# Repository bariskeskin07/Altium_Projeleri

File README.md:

# Altium_Projeleri
Olusturdugum altium projeleri

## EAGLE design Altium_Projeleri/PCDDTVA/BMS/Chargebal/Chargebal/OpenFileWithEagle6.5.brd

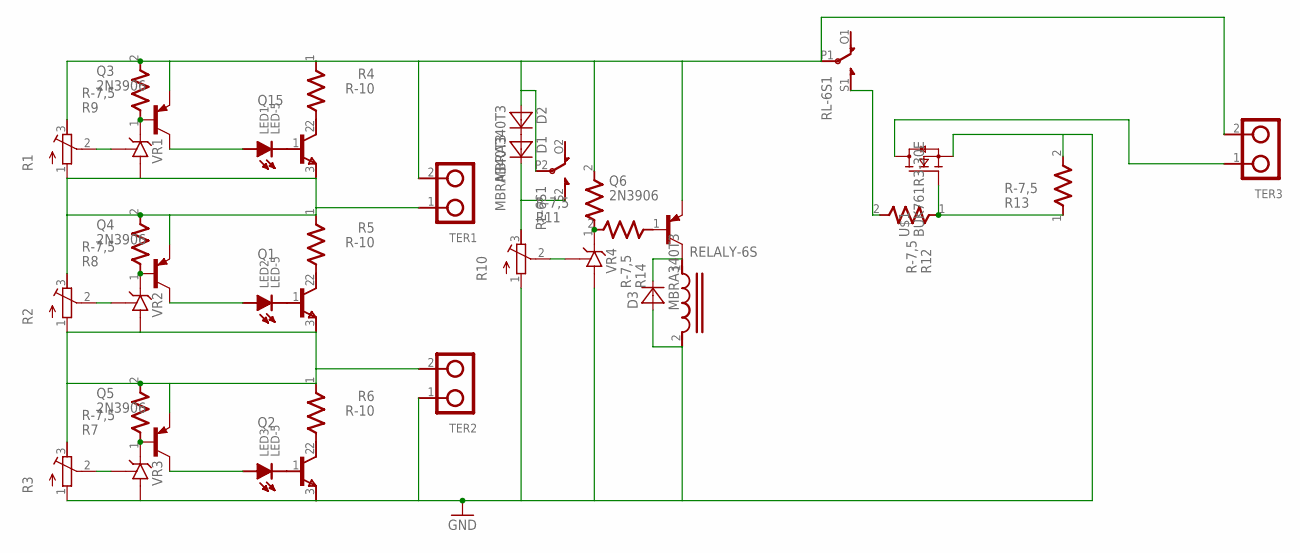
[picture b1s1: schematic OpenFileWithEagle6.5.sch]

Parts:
D1, D2, D3: MBRA340T3; SMA
LED1, LED2, LED3: LED-5; LED5
Q1, Q2, Q15: C1815; TO92L
Q3, Q4, Q5, Q6: 2N3906; TO92
R1, R2, R3, R10: R-TRIMM64W; RTRIM64W
R4, R5, R6: R-10
R7, R8, R9, R11, R12, R13, R14: R-7,5
RL-6S1: RELALY-6S; RELAY-6S
TER1, TER2, TER3: DOMINO-2; DOMI-2
U$1: BUK761R3-30E; SOT404
VR1, VR2, VR3, VR4: TL431CLP; TO92-CLP

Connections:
GND: D3.A, Q2.3 (E), R3.1 (A), R10.1 (A), R13.2, RL-6S1.2, TER2.1, U$1.3 (S), VR3.A, VR4.A
unnamed: LED1.K, Q15.1 (B)
unnamed: LED2.K, Q1.1 (B)
unnamed: LED3.K, Q2.1 (B)
unnamed: R10.2 (S), VR4.R
unnamed: R11.1, R14.2, VR4.C
unnamed: Q6.2 (B), R14.1
unnamed: R2.2 (S), VR2.R
unnamed: R3.2 (S), VR3.R
unnamed: Q3.2 (B), R9.1, VR1.C
unnamed: Q4.2 (B), R8.1, VR2.C
unnamed: Q5.2 (B), R7.1, VR3.C
unnamed: LED2.A, Q4.1 (C)
unnamed: LED3.A, Q5.1 (C)
unnamed: LED1.A, Q3.1 (C)
unnamed: Q15.2 (C), R4.2 (3)
unnamed: Q1.2 (C), R5.2 (3)
unnamed: Q2.2 (C), R6.2 (3)
unnamed: Q1.3 (E), Q5.3 (E), R2.1 (A), R3.3 (E), R6.1, R7.2, TER2.2, VR2.A
unnamed: Q4.3 (E), Q15.3 (E), R1.1 (A), R2.3 (E), R5.1, R8.2, TER1.1, VR1.A
unnamed: D2.A, Q3.3 (E), Q6.3 (E), R1.3 (E), R4.1, R9.2, R11.2, RL-6S1.P1, RL-6S1.P2, TER1.2, TER3.2
unnamed: R1.2 (S), VR1.R
unnamed: D3.C, Q6.1 (C), RL-6S1.1
unnamed: TER3.1, U$1.MB (D)
unnamed: D1.C, R10.3 (E), RL-6S1.S2 (S)
unnamed: R12.1, R13.1, U$1.1 (G)
unnamed: D1.A, D2.C
unnamed: R12.2, RL-6S1.S1 (S)

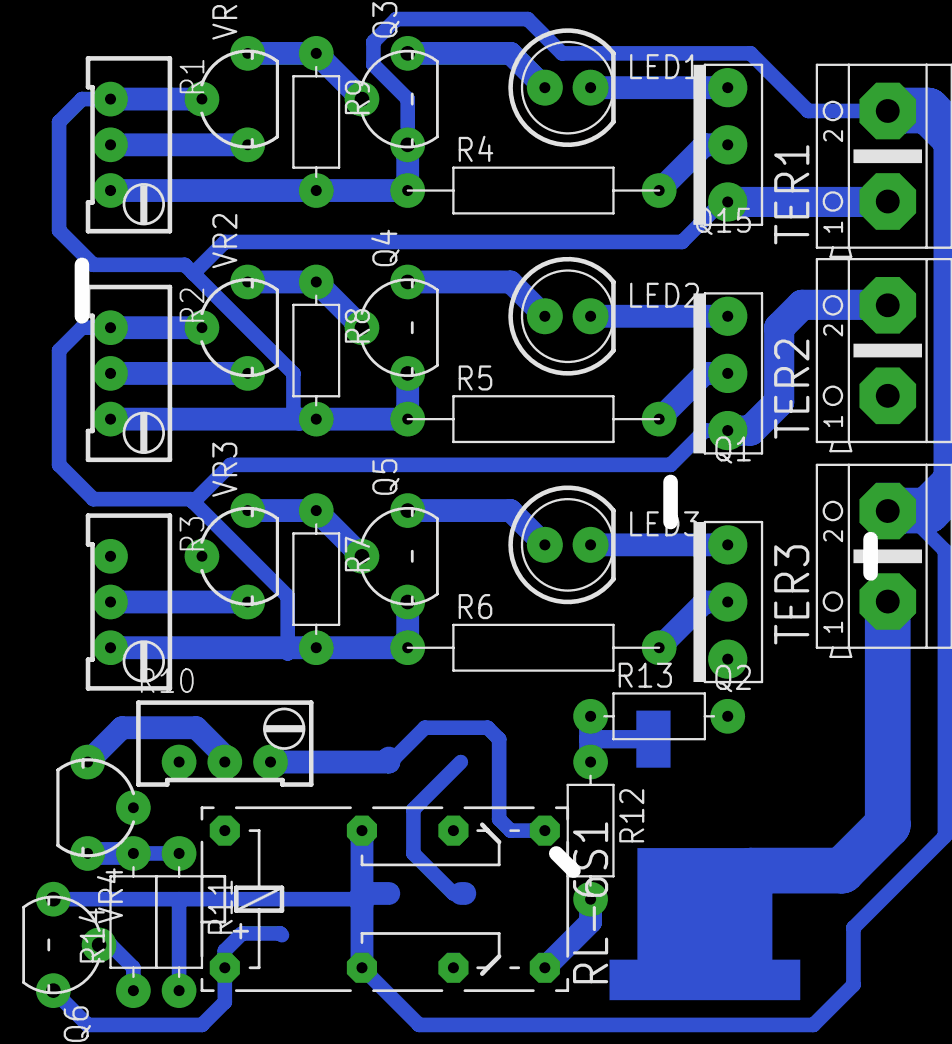
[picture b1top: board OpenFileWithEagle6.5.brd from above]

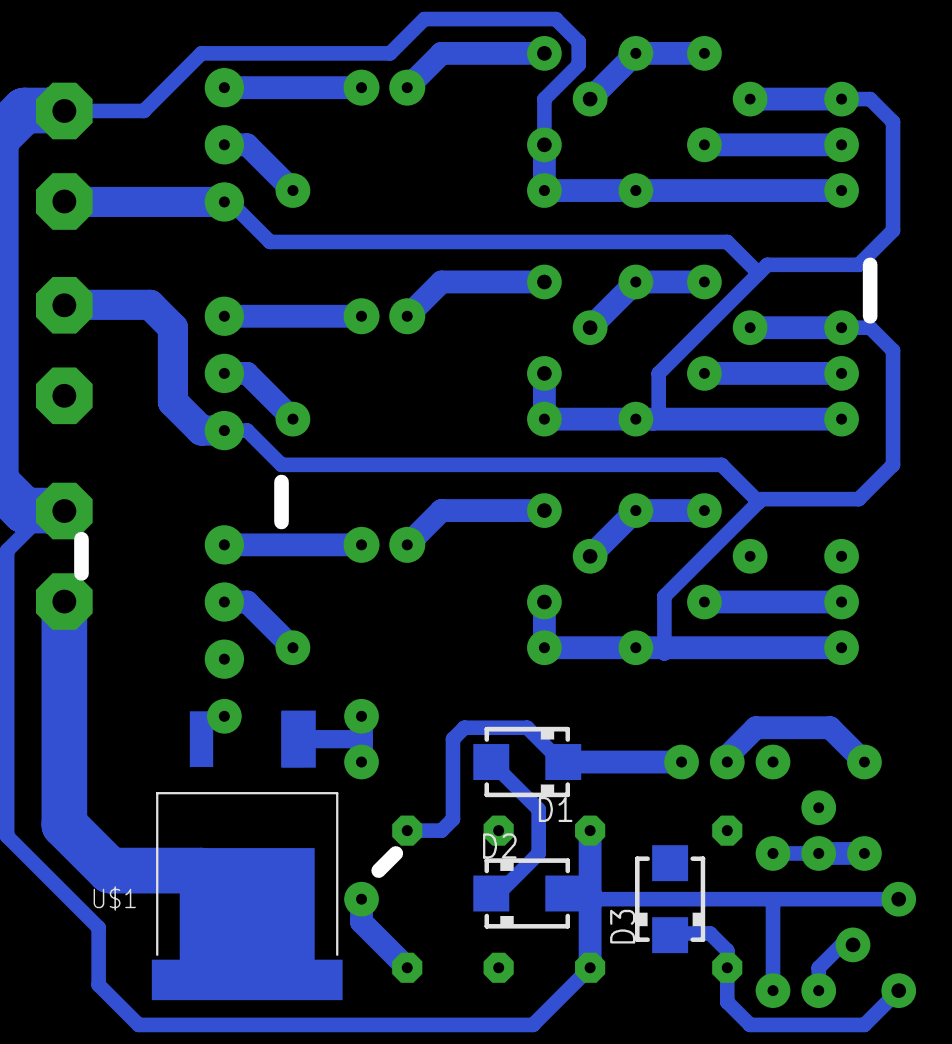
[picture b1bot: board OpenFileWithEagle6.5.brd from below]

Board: 2 copper layers, 36 parts (4 on the bottom side), 28 nets.

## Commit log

2021-01-30 Altium_Projeleri eklendi
